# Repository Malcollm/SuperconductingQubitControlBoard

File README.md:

# Superconducting Qubit Control Board

Custom FPGA-based control board for generating microwave I/Q signals used to drive superconducting qubits.

## Project Overview

This project is a hardware and FPGA control system for producing shaped control signals for superconducting qubit experiments. The board uses an FPGA to generate digital waveform data, a high-speed DAC to convert that data into analog I/Q signals, and an RF stage to upconvert the signals to microwave frequencies.

## Main Components

- FPGA digital control and waveform generation
- High-speed DAC for analog I/Q output
- TRF372017 RF modulator / PLL / VCO stage
- SPI control for configurable RF components
- Low-pass filtering between DAC and RF stages
- On-board power regulation and decoupling
- RF output through a controlled-impedance path to SMA

## Design Goals

- Generate programmable I/Q waveforms
- Support microwave signal generation for qubit control
- Keep the design modular and testable
- Document RF layout, DAC interfacing, FPGA control, and signal integrity design

## Current Status

This project is currently in development. The main focus is schematic design, PCB layout, FPGA communication, and validating the signal chain from the FPGA to the RF output.

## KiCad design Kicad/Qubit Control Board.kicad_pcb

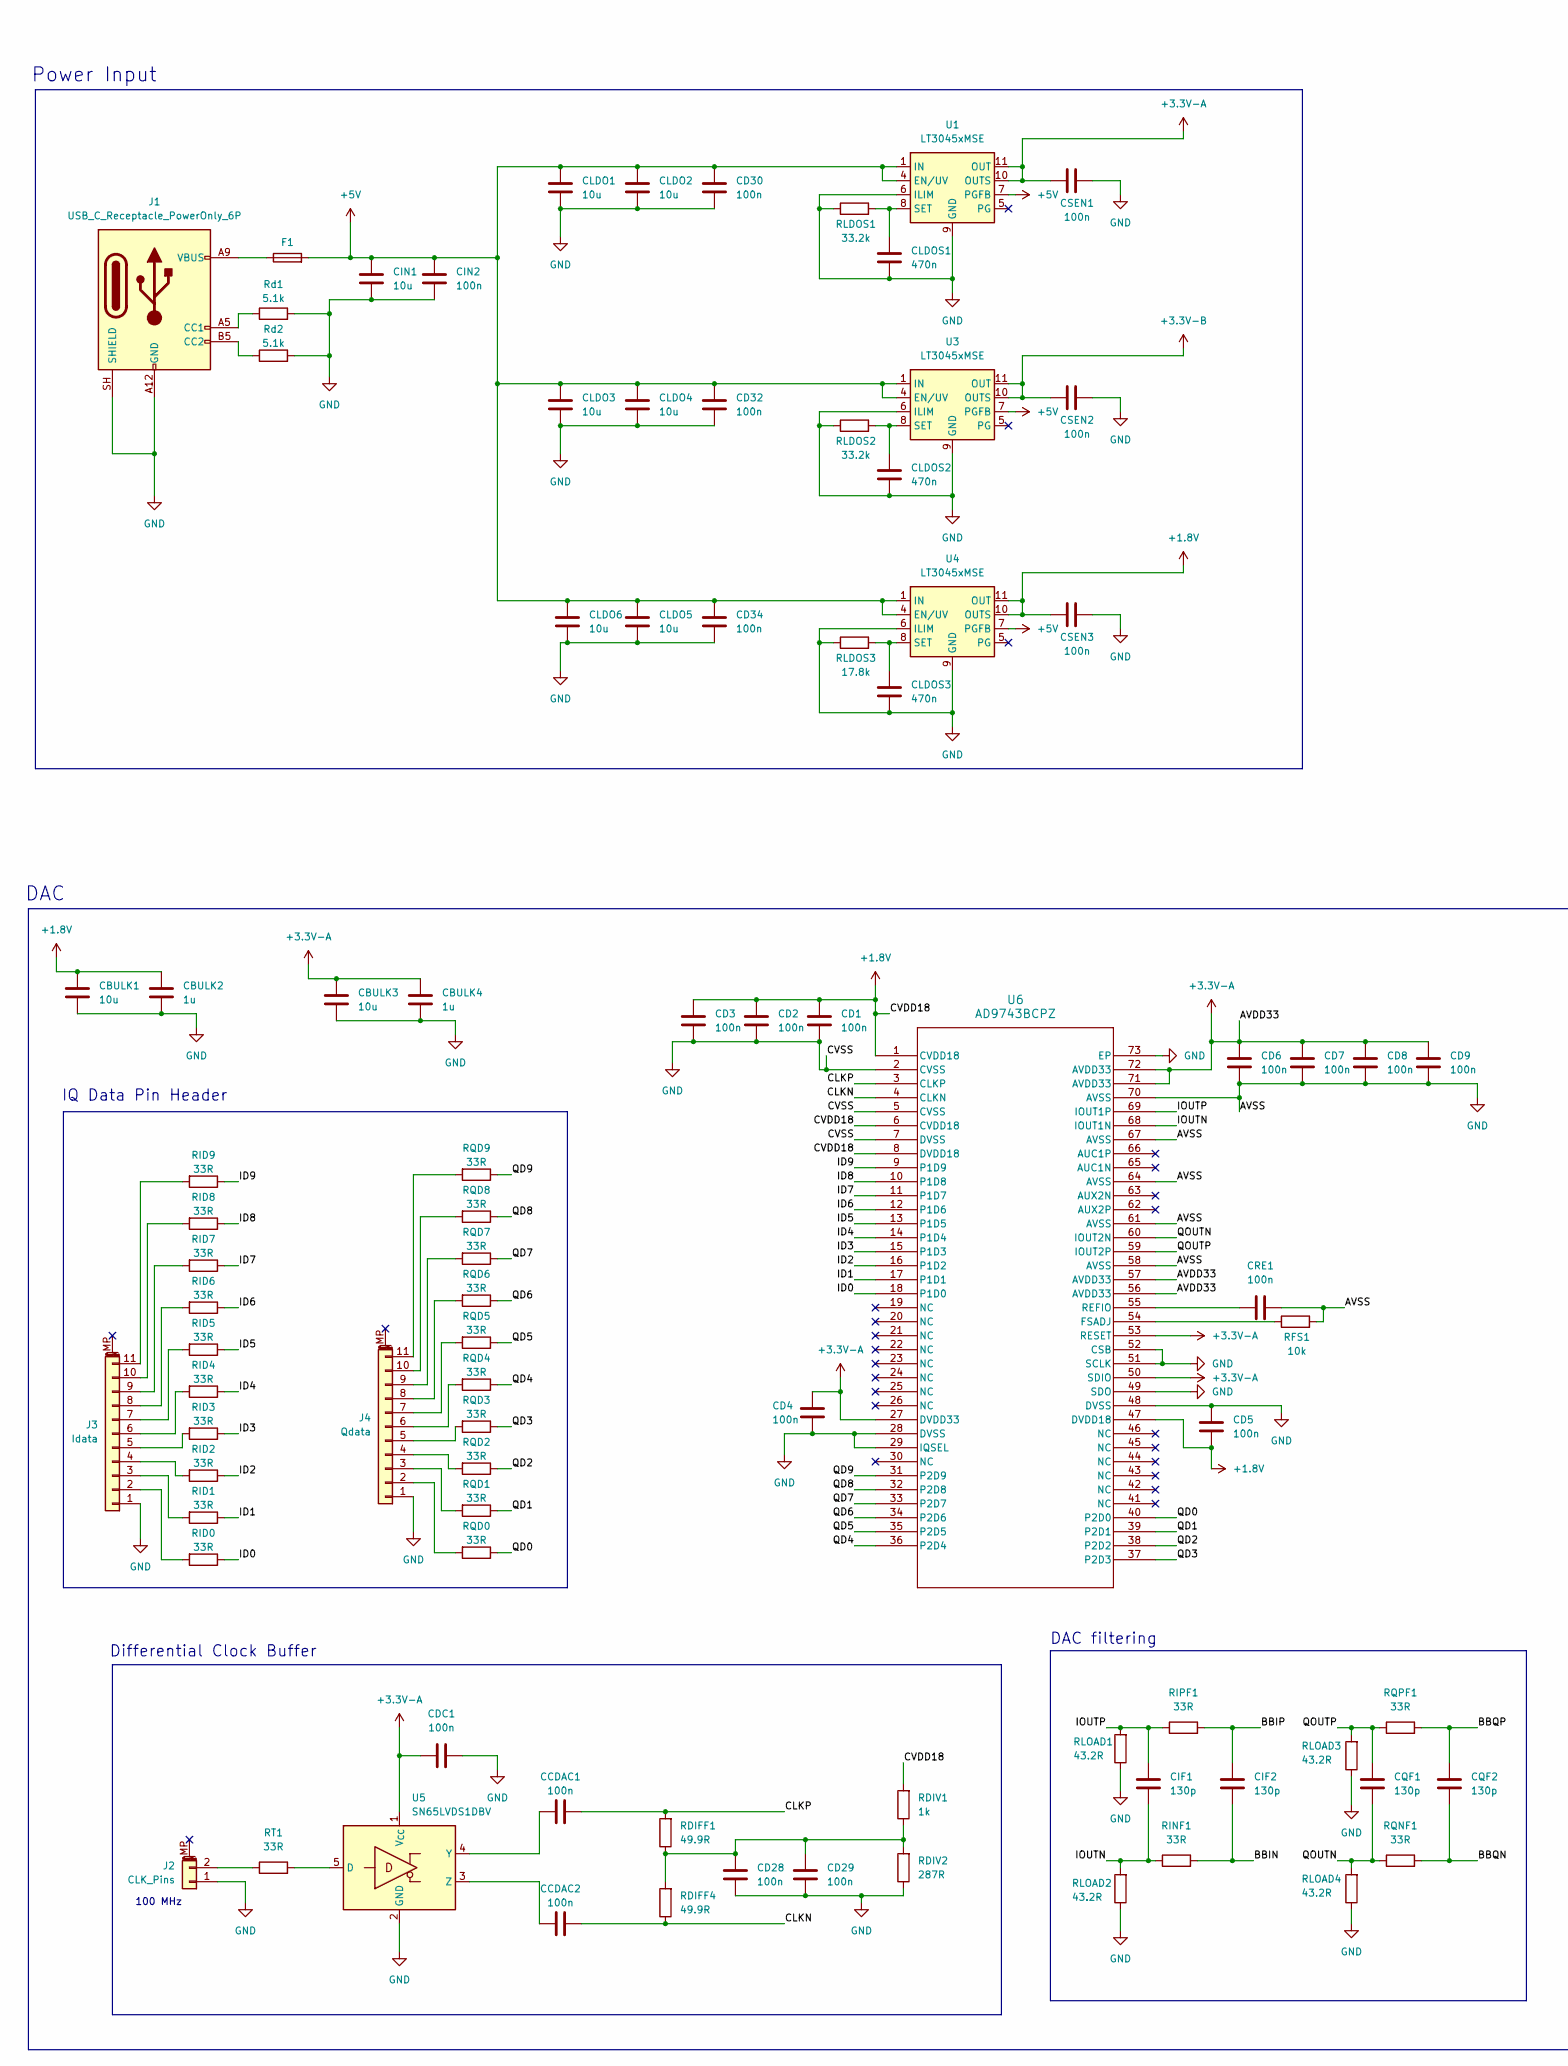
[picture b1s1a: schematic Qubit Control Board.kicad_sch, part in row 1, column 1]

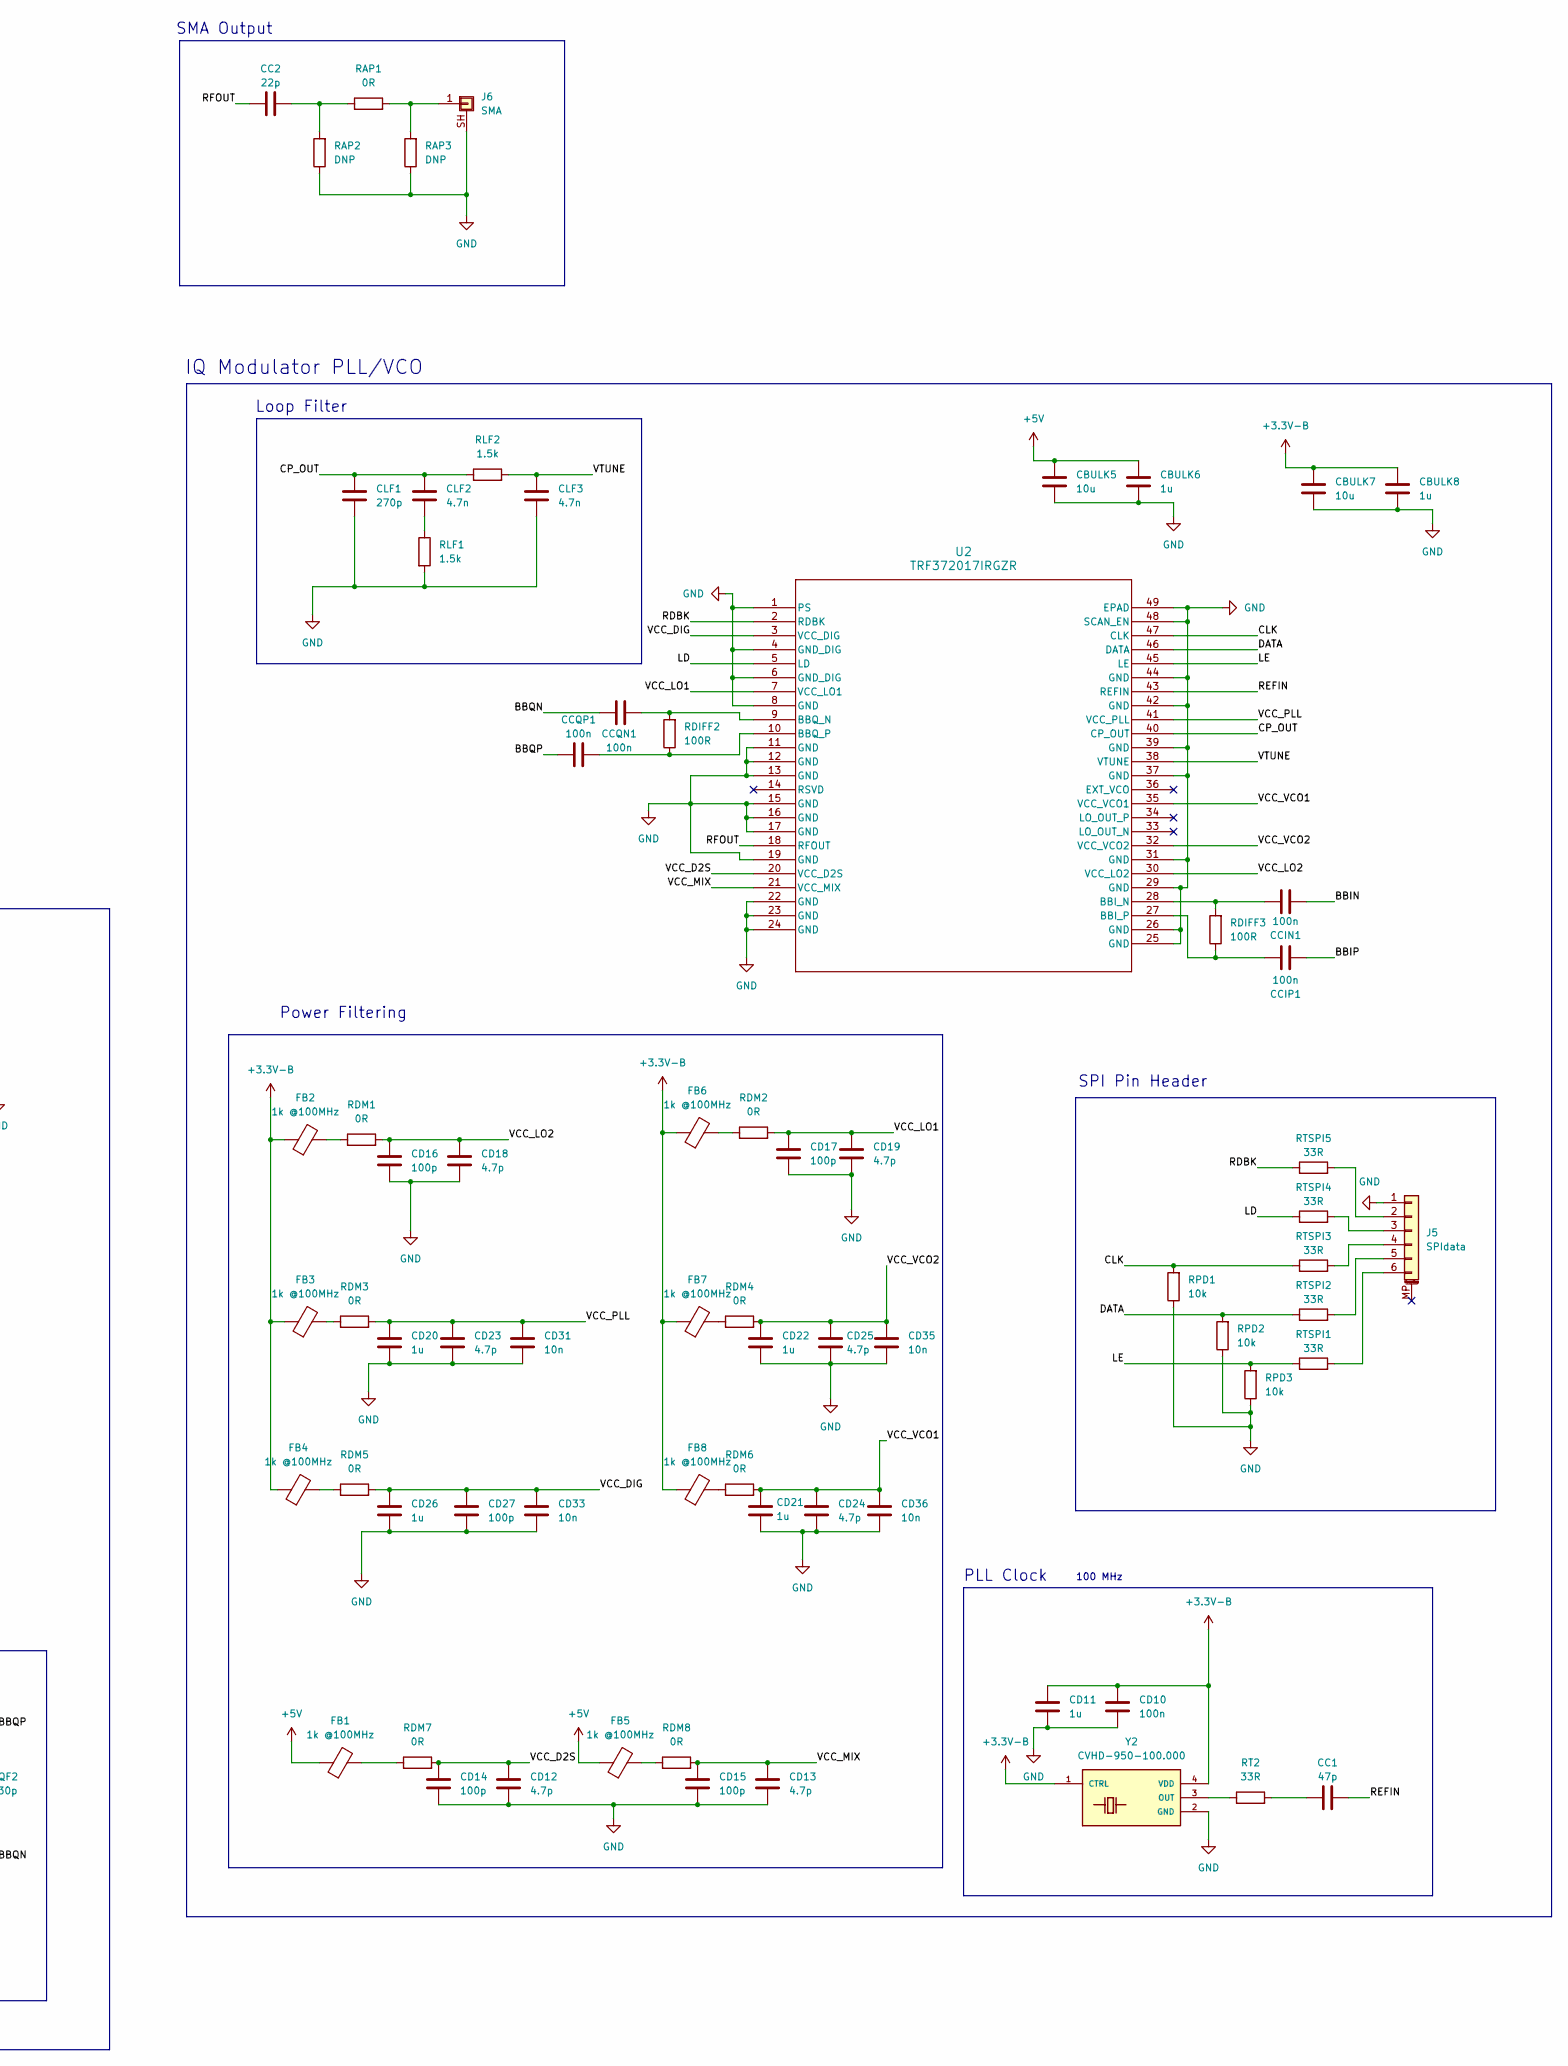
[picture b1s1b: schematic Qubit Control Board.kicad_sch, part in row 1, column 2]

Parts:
CBULK1, CBULK3, CBULK5, CBULK7: 10u; C_1206_3216Metric_Pad1.33x1.80mm_HandSolder
CBULK2, CBULK4, CBULK6, CBULK8: 1u; C_0805_2012Metric_Pad1.18x1.45mm_HandSolder
CC1: 47p; C_0603_1608Metric
CC2: 22p; C_0603_1608Metric
CCDAC1, CCDAC2: 100n; C_0603_1608Metric
CCIN1: 100n; C_0603_1608Metric
CCIP1: 100n; C_0603_1608Metric
CCQN1: 100n; C_0603_1608Metric
CCQP1: 100n; C_0603_1608Metric
CD1, CD2, CD3, CD4, CD5, CD6, CD7, CD8, CD9, CD10, CD28, CD29, CD30, CD32, CD34: 100n; C_0402_1005Metric
CD11, CD20, CD21, CD22, CD26: 1u; C_0603_1608Metric
CD12, CD13, CD18, CD19, CD23, CD24, CD25: 4.7p; C_0402_1005Metric
CD14, CD15, CD16, CD17, CD27: 100p; C_0402_1005Metric
CD31, CD33, CD35, CD36: 10n; C_0402_1005Metric
CDC1: 100n; C_0402_1005Metric
CIF1, CIF2: 130p; C_0603_1608Metric
CIN1: 10u; C_1206_3216Metric_Pad1.33x1.80mm_HandSolder
CIN2: 100n; C_0603_1608Metric
CLDO1, CLDO2: 10u; C_0603_1608Metric
CLDO3, CLDO4, CLDO5, CLDO6: 10u; C_1206_3216Metric_Pad1.33x1.80mm_HandSolder
CLDOS1, CLDOS2, CLDOS3: 470n; C_0402_1005Metric
CLF1: 270p; C_0402_1005Metric
CLF2, CLF3: 4.7n; C_0402_1005Metric
CQF1, CQF2: 130p; C_0603_1608Metric
CRE1: 100n; C_0603_1608Metric
CSEN1, CSEN2, CSEN3: 100n; C_0402_1005Metric
F1: Fuse_1206_3216Metric
FB1, FB2, FB3, FB4, FB5, FB6, FB7, FB8: 1k @100MHz; L_0603_1608Metric_Pad1.05x0.95mm_HandSolder
J1: USB_C_Receptacle_PowerOnly_6P; USB_C_Receptacle_GCT_USB4135-GF-A_6P_TopMnt_Horizontal
J2: CLK_Pins; PinHeader_1x02_P1.00mm_Vertical
J3: Idata; PinHeader_1x11_P1.00mm_Vertical
J4: Qdata; PinHeader_1x11_P1.00mm_Vertical
J5: SPIdata; PinHeader_1x06_P1.00mm_Vertical
J6: SMA; SMA_Molex_73251-1153_EdgeMount_Horizontal
RAP1: 0R; R_0603_1608Metric
RAP2, RAP3: DNP; R_0603_1608Metric
RDIFF1, RDIFF4: 49.9R; R_0603_1608Metric
RDIFF2, RDIFF3: 100R; R_0402_1005Metric
RDIV1: 1k; R_0603_1608Metric
RDIV2: 287R; R_0603_1608Metric
RDM1, RDM2, RDM3, RDM4, RDM5, RDM6, RDM7, RDM8: 0R; R_0603_1608Metric
RFS1: 10k; R_0603_1608Metric
RID0, RID1, RID2, RID3, RID4, RID5, RID6, RID7, RID8, RID9: 33R; R_0402_1005Metric
RINF1: 33R; R_0603_1608Metric
RIPF1: 33R; R_0603_1608Metric
RLDOS1, RLDOS2: 33.2k; R_0603_1608Metric
RLDOS3: 17.8k; R_0603_1608Metric
RLF1, RLF2: 1.5k; R_0402_1005Metric
RLOAD1, RLOAD2, RLOAD3, RLOAD4: 43.2R; R_0603_1608Metric
RPD1, RPD2, RPD3: 10k; R_0603_1608Metric
RQD0, RQD1, RQD2, RQD3, RQD4, RQD5, RQD6, RQD7, RQD8, RQD9: 33R; R_0402_1005Metric
RQNF1: 33R; R_0603_1608Metric
RQPF1: 33R; R_0603_1608Metric
RT1, RT2: 33R; R_0402_1005Metric
RTSPI1, RTSPI2, RTSPI3, RTSPI4, RTSPI5: 33R; R_0402_1005Metric
Rd1, Rd2: 5.1k; R_0603_1608Metric
U1, U3, U4: LT3045xMSE; MSOP-12-1EP_3x4.039mm_P0.65mm_EP1.651x2.845mm
U2: TRF372017IRGZR; RGZ48_5P6X5P6
U5: SN65LVDS1DBV; SOT-23-5
U6: AD9743BCPZ; CP-72-1_ADI-M
Y2: CVHD-950-100.000; OSCSC508P1420X914X530-4N

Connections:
+1.8V: CBULK1.1, CBULK2.1, CD1.2, CD2.2, CD3.2, CD5.1, CSEN3.2, RDIV1.2, U4.10 (OUTS), U4.11 (OUT), U4.12 (OUT), U6.1 (CVDD18), U6.6 (CVDD18), U6.8 (DVDD18), U6.47 (DVDD18)
+3.3V-A: CBULK3.1, CBULK4.1, CD4.2, CD6.2, CD7.2, CD8.2, CD9.2, CDC1.1, CSEN1.2, U1.10 (OUTS), U1.11 (OUT), U1.12 (OUT), U5.1 (V_{CC}), U6.27 (DVDD33), U6.50 (SDIO), U6.53 (RESET), U6.56 (AVDD33), U6.57 (AVDD33), U6.71 (AVDD33), U6.72 (AVDD33)
+3.3V-B: CBULK7.1, CBULK8.1, CD10.2, CD11.2, CSEN2.2, FB2.1, FB3.1, FB4.1, FB6.1, FB7.1, FB8.1, U3.10 (OUTS), U3.11 (OUT), U3.12 (OUT), Y2.1 (CTRL), Y2.4 (VDD)
+5V: CBULK5.1, CBULK6.1, CD30.2, CD32.2, CD34.2, CIN1.1, CIN2.1, CLDO1.1, CLDO2.1, CLDO3.1, CLDO4.1, CLDO5.1, CLDO6.1, F1.2, FB1.1, FB5.1, U1.1 (IN), U1.2 (IN), U1.3 (IN), U1.4 (EN/UV), U1.7 (PGFB), U3.1 (IN), U3.2 (IN), U3.3 (IN), U3.4 (EN/UV), U3.7 (PGFB), U4.1 (IN), U4.2 (IN), U4.3 (IN), U4.4 (EN/UV), U4.7 (PGFB)
/BBIN: CCIN1.1, CIF2.2, RINF1.2
/BBIP: CCIP1.1, CIF2.1, RIPF1.2
/BBQN: CCQN1.1, CQF2.2, RQNF1.2
/BBQP: CCQP1.1, CQF2.1, RQPF1.2
/CLK: RPD1.2, RTSPI3.1, U2.47 (CLK)
/CLKN: CCDAC2.2, RDIFF4.1, U6.4 (CLKN)
/CLKP: CCDAC1.2, RDIFF1.2, U6.3 (CLKP)
/CP_OUT: CLF1.1, CLF2.1, RLF2.1, U2.40 (CP_OUT)
/DATA: RPD2.2, RTSPI2.1, U2.46 (DATA)
/ID0: RID0.1, U6.18 (P1D0)
/ID1: RID1.1, U6.17 (P1D1)
/ID2: RID2.1, U6.16 (P1D2)
/ID3: RID3.1, U6.15 (P1D3)
/ID4: RID4.1, U6.14 (P1D4)
/ID5: RID5.1, U6.13 (P1D5)
/ID6: RID6.1, U6.12 (P1D6)
/ID7: RID7.1, U6.11 (P1D7)
/ID8: RID8.1, U6.10 (P1D8)
/ID9: RID9.1, U6.9 (P1D9)
/IOUTN: CIF1.2, RINF1.1, RLOAD2.2, U6.68 (IOUT1N)
/IOUTP: CIF1.1, RIPF1.1, RLOAD1.2, U6.69 (IOUT1P)
/LD: RTSPI4.1, U2.5 (LD)
/LE: RPD3.2, RTSPI1.1, U2.45 (LE)
/QD0: RQD0.1, U6.40 (P2D0)
/QD1: RQD1.1, U6.39 (P2D1)
/QD2: RQD2.1, U6.38 (P2D2)
/QD3: RQD3.1, U6.37 (P2D3)
/QD4: RQD4.1, U6.36 (P2D4)
/QD5: RQD5.1, U6.35 (P2D5)
/QD6: RQD6.1, U6.34 (P2D6)
/QD7: RQD7.1, U6.33 (P2D7)
/QD8: RQD8.1, U6.32 (P2D8)
/QD9: RQD9.1, U6.31 (P2D9)
/QOUTN: CQF1.2, RLOAD4.2, RQNF1.1, U6.60 (IOUT2N)
/QOUTP: CQF1.1, RLOAD3.2, RQPF1.1, U6.59 (IOUT2P)
/RDBK: RTSPI5.1, U2.2 (RDBK)
/REFIN: CC1.2, U2.43 (REFIN)
/RFOUT: CC2.1, U2.18 (RFOUT)
/VCC_D2S: CD12.2, CD14.2, RDM7.2, U2.20 (VCC_D2S)
/VCC_DIG: CD26.2, CD27.2, CD33.2, RDM5.2, U2.3 (VCC_DIG)
/VCC_LO1: CD17.2, CD19.2, RDM2.2, U2.7 (VCC_LO1)
/VCC_LO2: CD16.2, CD18.2, RDM1.2, U2.30 (VCC_LO2)
/VCC_MIX: CD13.2, CD15.2, RDM8.2, U2.21 (VCC_MIX)
/VCC_PLL: CD20.2, CD23.2, CD31.2, RDM3.2, U2.41 (VCC_PLL)
/VCC_VCO1: CD21.2, CD24.2, CD36.2, RDM6.2, U2.35 (VCC_VCO1)
/VCC_VCO2: CD22.2, CD25.2, CD35.2, RDM4.2, U2.32 (VCC_VCO2)
/VTUNE: CLF3.1, RLF2.2, U2.38 (VTUNE)
GND: CBULK1.2, CBULK2.2, CBULK3.2, CBULK4.2, CBULK5.2, CBULK6.2, CBULK7.2, CBULK8.2, CD1.1, CD2.1, CD3.1, CD4.1, CD5.2, CD6.1, CD7.1, CD8.1, CD9.1, CD10.1, CD11.1, CD12.1, CD13.1, CD14.1, CD15.1, CD16.1, CD17.1, CD18.1, CD19.1, CD20.1, CD21.1, CD22.1, CD23.1, CD24.1, CD25.1, CD26.1, CD27.1, CD28.1, CD29.1, CD30.1, CD31.1, CD32.1, CD33.1, CD34.1, CD35.1, CD36.1, CDC1.2, CIN1.2, CIN2.2, CLDO1.2, CLDO2.2, CLDO3.2, CLDO4.2, CLDO5.2, CLDO6.2, CLDOS1.1, CLDOS2.1, CLDOS3.1, CLF1.2, CLF3.2, CRE1.1, CSEN1.1, CSEN2.1, CSEN3.1, J1.A12 (GND), J1.B12 (GND), J1.SH (SHIELD), J2.1, J3.1, J4.1, J5.1, J6.SH (Shield), RAP2.1, RAP3.1, RDIV2.1, RFS1.2, RLDOS1.1, RLDOS2.1, RLDOS3.1, RLF1.2, RLOAD1.1, RLOAD2.1, RLOAD3.1, RLOAD4.1, RPD1.1, RPD2.1, RPD3.1, Rd1.2, Rd2.2, U1.6 (ILIM), U1.9 (GND), U1.13 (GND), U2.1 (PS), U2.4 (GND_DIG), U2.6 (GND_DIG), U2.8 (GND), U2.11 (GND), U2.12 (GND), U2.13 (GND), U2.15 (GND), U2.16 (GND), U2.17 (GND), U2.19 (GND), U2.22 (GND), U2.23 (GND), U2.24 (GND), U2.25 (GND), U2.26 (GND), U2.29 (GND), U2.31 (GND), U2.37 (GND), U2.39 (GND), U2.42 (GND), U2.44 (GND), U2.48 (SCAN_EN), U2.49 (EPAD), U3.6 (ILIM), U3.9 (GND), U3.13 (GND), U4.6 (ILIM), U4.9 (GND), U4.13 (GND), U5.2 (GND), U6.2 (CVSS), U6.5 (CVSS), U6.7 (DVSS), U6.28 (DVSS), U6.29 (IQSEL), U6.48 (DVSS), U6.49 (SDO), U6.51 (SCLK), U6.52 (CSB), U6.58 (AVSS), U6.61 (AVSS), U6.64 (AVSS), U6.67 (AVSS), U6.70 (AVSS), U6.73 (EP), Y2.2 (GND)
unnamed: CC1.1, RT2.2
unnamed: CC2.2, RAP1.1, RAP2.2
unnamed: CD28.2, CD29.2, RDIFF1.1, RDIFF4.2, RDIV1.1, RDIV2.2
unnamed: CLF2.2, RLF1.1
unnamed: F1.1, J1.A9 (VBUS), J1.B9 (VBUS)
unnamed: FB1.2, RDM7.1
unnamed: FB2.2, RDM1.1
unnamed: FB3.2, RDM3.1
unnamed: FB4.2, RDM5.1
unnamed: FB5.2, RDM8.1
unnamed: FB6.2, RDM2.1
unnamed: FB7.2, RDM4.1
unnamed: FB8.2, RDM6.1
unnamed: J1.A5 (CC1), Rd1.1
unnamed: J1.B5 (CC2), Rd2.1
unnamed: J2.2, RT1.1
unnamed: J3.2, RID0.2
unnamed: J3.3, RID1.2
unnamed: J3.4, RID2.2
unnamed: J3.5, RID3.2
unnamed: J3.6, RID4.2
unnamed: J3.7, RID5.2
unnamed: J3.8, RID6.2
unnamed: J3.9, RID7.2
unnamed: J3.10, RID8.2
unnamed: J3.11, RID9.2
unnamed: J4.2, RQD0.2
unnamed: J4.3, RQD1.2
unnamed: J4.4, RQD2.2
unnamed: J4.5, RQD3.2
unnamed: J4.6, RQD4.2
unnamed: J4.7, RQD5.2
unnamed: J4.8, RQD6.2
unnamed: J4.9, RQD7.2
unnamed: J4.10, RQD8.2
unnamed: J4.11, RQD9.2
unnamed: J5.2, RTSPI5.2
unnamed: J5.3, RTSPI4.2
unnamed: J5.4, RTSPI3.2
unnamed: J5.5, RTSPI2.2
unnamed: J5.6, RTSPI1.2
unnamed: J6.1 (Pin_1_1), RAP1.2, RAP3.2
unnamed: CLDOS1.2, RLDOS1.2, U1.8 (SET)
unnamed: CCIN1.2, RDIFF3.2, U2.28 (BBI_N)
unnamed: CCIP1.2, RDIFF3.1, U2.27 (BBI_P)
unnamed: CCQN1.2, RDIFF2.2, U2.9 (BBQ_N)
unnamed: CCQP1.2, RDIFF2.1, U2.10 (BBQ_P)
unnamed: CLDOS2.2, RLDOS2.2, U3.8 (SET)
unnamed: CLDOS3.2, RLDOS3.2, U4.8 (SET)
unnamed: RT1.2, U5.5 (D)
unnamed: CCDAC1.1, U5.4 (Y)
unnamed: CCDAC2.1, U5.3 (Z)
unnamed: RFS1.1, U6.54 (FSADJ)
unnamed: CRE1.2, U6.55 (REFIO)
unnamed: RT2.1, Y2.3 (OUT)

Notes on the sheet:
SMA Output
100 MHz
SPI Pin Header
Power Filtering
DAC filtering
Loop Filter
IQ Data Pin Header
DAC
IQ Modulator PLL/VCO
Differential Clock Buffer
Power Input
PLL Clock

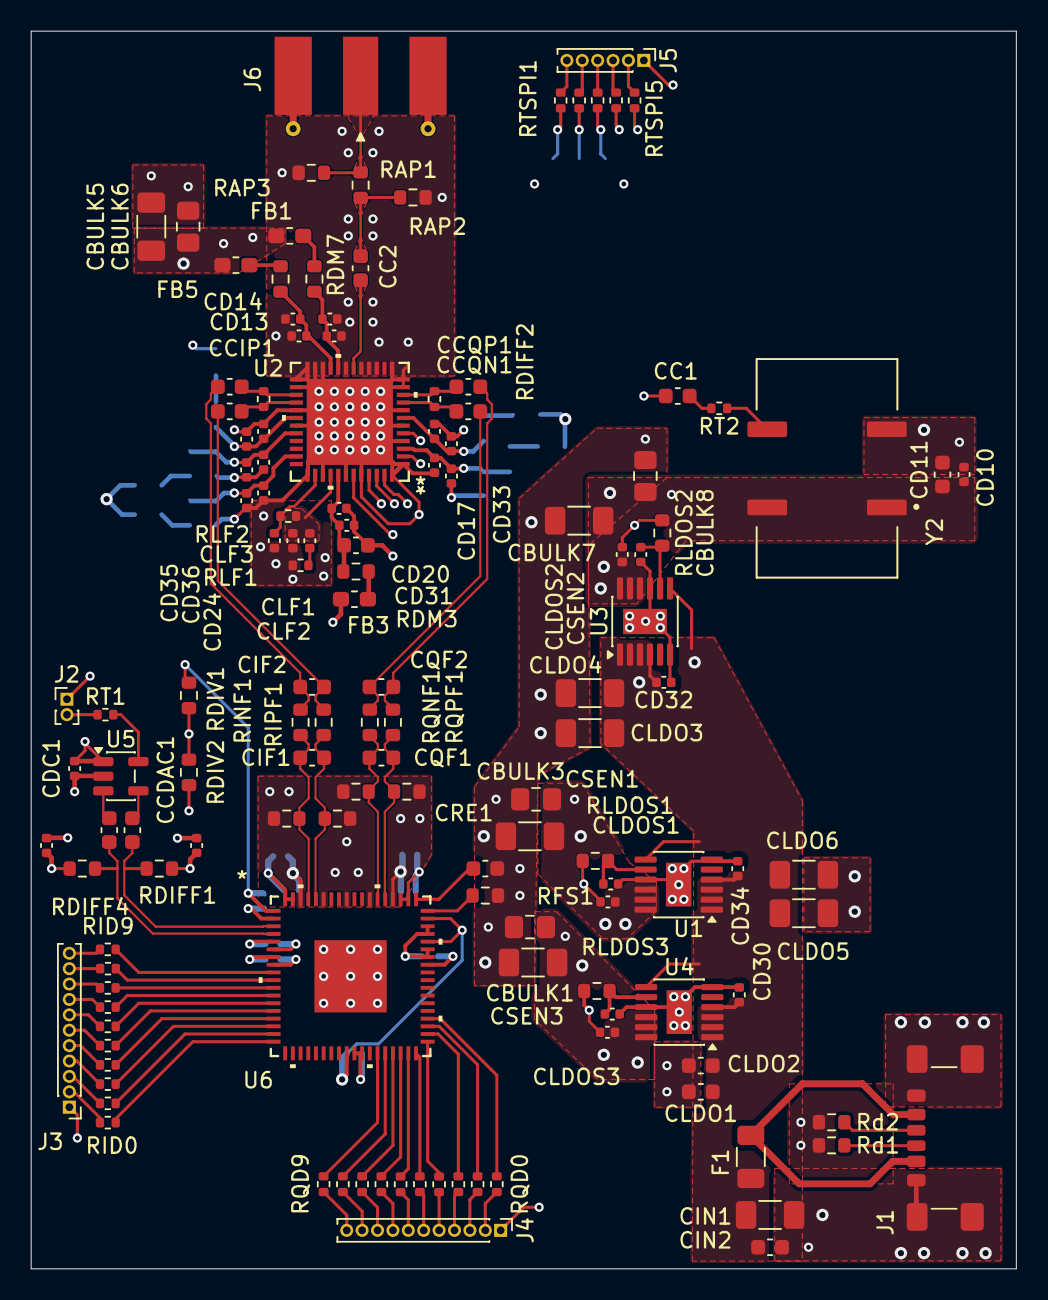
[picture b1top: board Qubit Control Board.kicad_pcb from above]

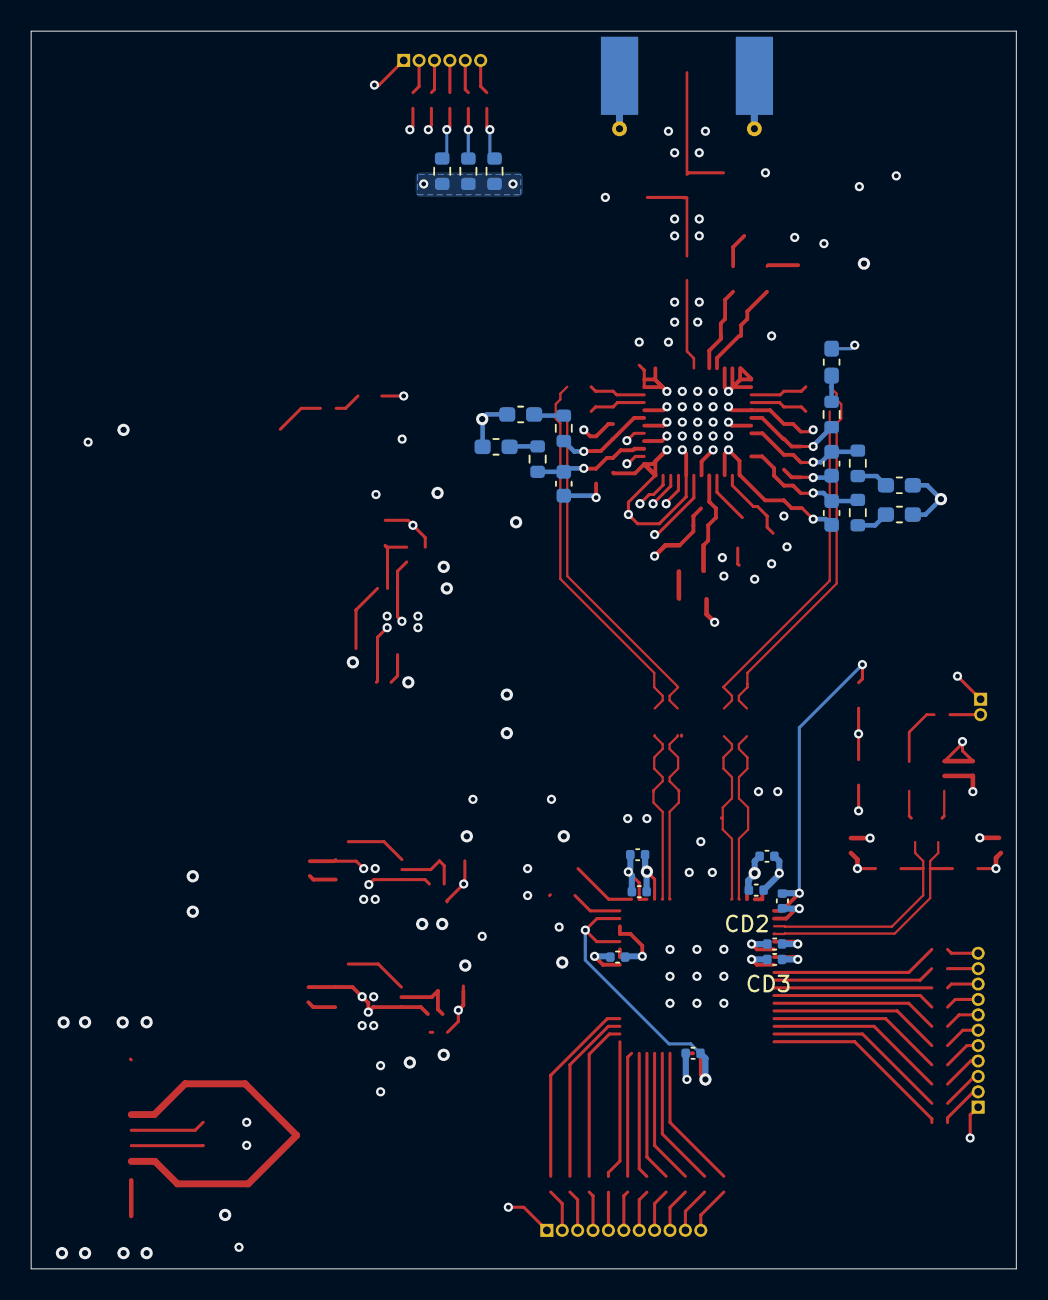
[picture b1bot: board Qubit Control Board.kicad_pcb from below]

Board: 6 copper layers, 64.0 x 80.4 mm, 160 parts (25 on the bottom side), 107 nets.

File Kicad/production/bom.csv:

Designator,Footprint,Quantity,Value,LCSC Part #
"CBULK1, CBULK3, CBULK5, CBULK7, CIN1, CLDO3, CLDO4, CLDO5, CLDO6",1206,9,10u,
"CBULK2, CBULK4, CBULK6, CBULK8",0805,4,1u,
CC1,0603,1,47p,
CC2,0603,1,22p,
"CCDAC1, CCDAC2, CCIN1, CCIP1, CCQN1, CCQP1, CIN2, CRE1",0603,8,100n,
"CD1, CD10, CD2, CD28, CD29, CD3, CD30, CD32, CD34, CD4, CD5, CD6, CD7, CD8, CD9, CDC1, CSEN1, CSEN2, CSEN3",0402,19,100n,
"CD11, CD20, CD21, CD22, CD26",0603,5,1u,
"CD12, CD13, CD18, CD19, CD23, CD24, CD25",0402,7,4.7p,
"CD14, CD15, CD16, CD17, CD27",0402,5,100p,
"CD31, CD33, CD35, CD36",0402,4,10n,
"CIF1, CIF2, CQF1, CQF2",0603,4,130p,
"CLDO1, CLDO2",0603,2,10u,
"CLDOS1, CLDOS2, CLDOS3",0402,3,470n,
CLF1,0402,1,270p,
"CLF2, CLF3",0402,2,4.7n,
F1,1206,1,~,
"FB1, FB2, FB3, FB4, FB5, FB6, FB7, FB8",0603,8,1k @100MHz,
J1,USB_C_Receptacle_GCT_USB4135-GF-A_6P_TopMnt_Horizontal,1,USB_C_Receptacle_PowerOnly_6P,
J2,PinHeader_1x02_P1.00mm_Vertical,1,CLK_Pins,
J3,PinHeader_1x11_P1.00mm_Vertical,1,Idata,
J4,PinHeader_1x11_P1.00mm_Vertical,1,Qdata,
J5,PinHeader_1x06_P1.00mm_Vertical,1,SPIdata,
J6,SMA_Molex_73251-1153_EdgeMount_Horizontal,1,SMA,
"RAP1, RDM1, RDM2, RDM3, RDM4, RDM5, RDM6, RDM7, RDM8",0603,9,0R,
"RAP2, RAP3",0603,2,DNP,
"RD1, RD2",0603,2,5.1k,
"RDIFF1, RDIFF4",0603,2,49.9R,
"RDIFF2, RDIFF3",0402,2,100R,
RDIV1,0603,1,1k,
RDIV2,0603,1,287R,
"RFS1, RPD1, RPD2, RPD3",0603,4,10k,
"RID0, RID1, RID2, RID3, RID4, RID5, RID6, RID7, RID8, RID9, RQD0, RQD1, RQD2, RQD3, RQD4, RQD5, RQD6, RQD7, RQD8, RQD9, RT1, RT2, RTSPI1, RTSPI2, RTSPI3, RTSPI4, RTSPI5",0402,27,33R,
"RINF1, RIPF1, RQNF1, RQPF1",0603,4,33R,
"RLDOS1, RLDOS2",0603,2,33.2k,
RLDOS3,0603,1,17.8k,
"RLF1, RLF2",0402,2,1.5k,
"RLOAD1, RLOAD2, RLOAD3, RLOAD4",0603,4,43.2R,
"U1, U3, U4",MSOP-12-1EP_3x4.039mm_P0.65mm_EP1.651x2.845mm,3,LT3045xMSE,
U2,RGZ48_5P6X5P6,1,TRF372017IRGZR,
U5,SOT-23-5,1,SN65LVDS1DBV,
U6,CP-72-1_ADI-M,1,AD9743BCPZ,
Y2,OSCSC508P1420X914X530-4N,1,CVHD-950-100.000,

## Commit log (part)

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2026-05-13 Add project description for superconducting qubit simulation
2026-05-14 Added display method is BlochVector class
2026-05-24 Added pcb files
2026-05-24 Updated README file
    Expanded project description to include details about the hardware and software platform for superconducting qubit control experiments.
2026-06-27 Input power set up
2026-06-28 Added DAC
2026-06-28 Added DAC filtering
2026-06-28 started on IQ mixer and added oscillator
2026-06-28 VCO power input filtering
2026-06-28 Finished IQ modulator with PLL/VCO
2026-06-29 Added FPGA files for verilog
2026-06-29 Enhance README with project details and structure
    Expanded project description and added details about main components, design goals, repository structure, and current status.
2026-06-29 Remove repository structure details from README
    Removed the repository structure section from the README.
2026-06-29 DAC clock changed and RC filter changes
